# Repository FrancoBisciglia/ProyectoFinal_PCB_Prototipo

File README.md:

# ProyectoFinal_PCB_Prototipo
 PCB de la placa prototipo del Sistema de Automatización para Huertas Hidropónicas NFT

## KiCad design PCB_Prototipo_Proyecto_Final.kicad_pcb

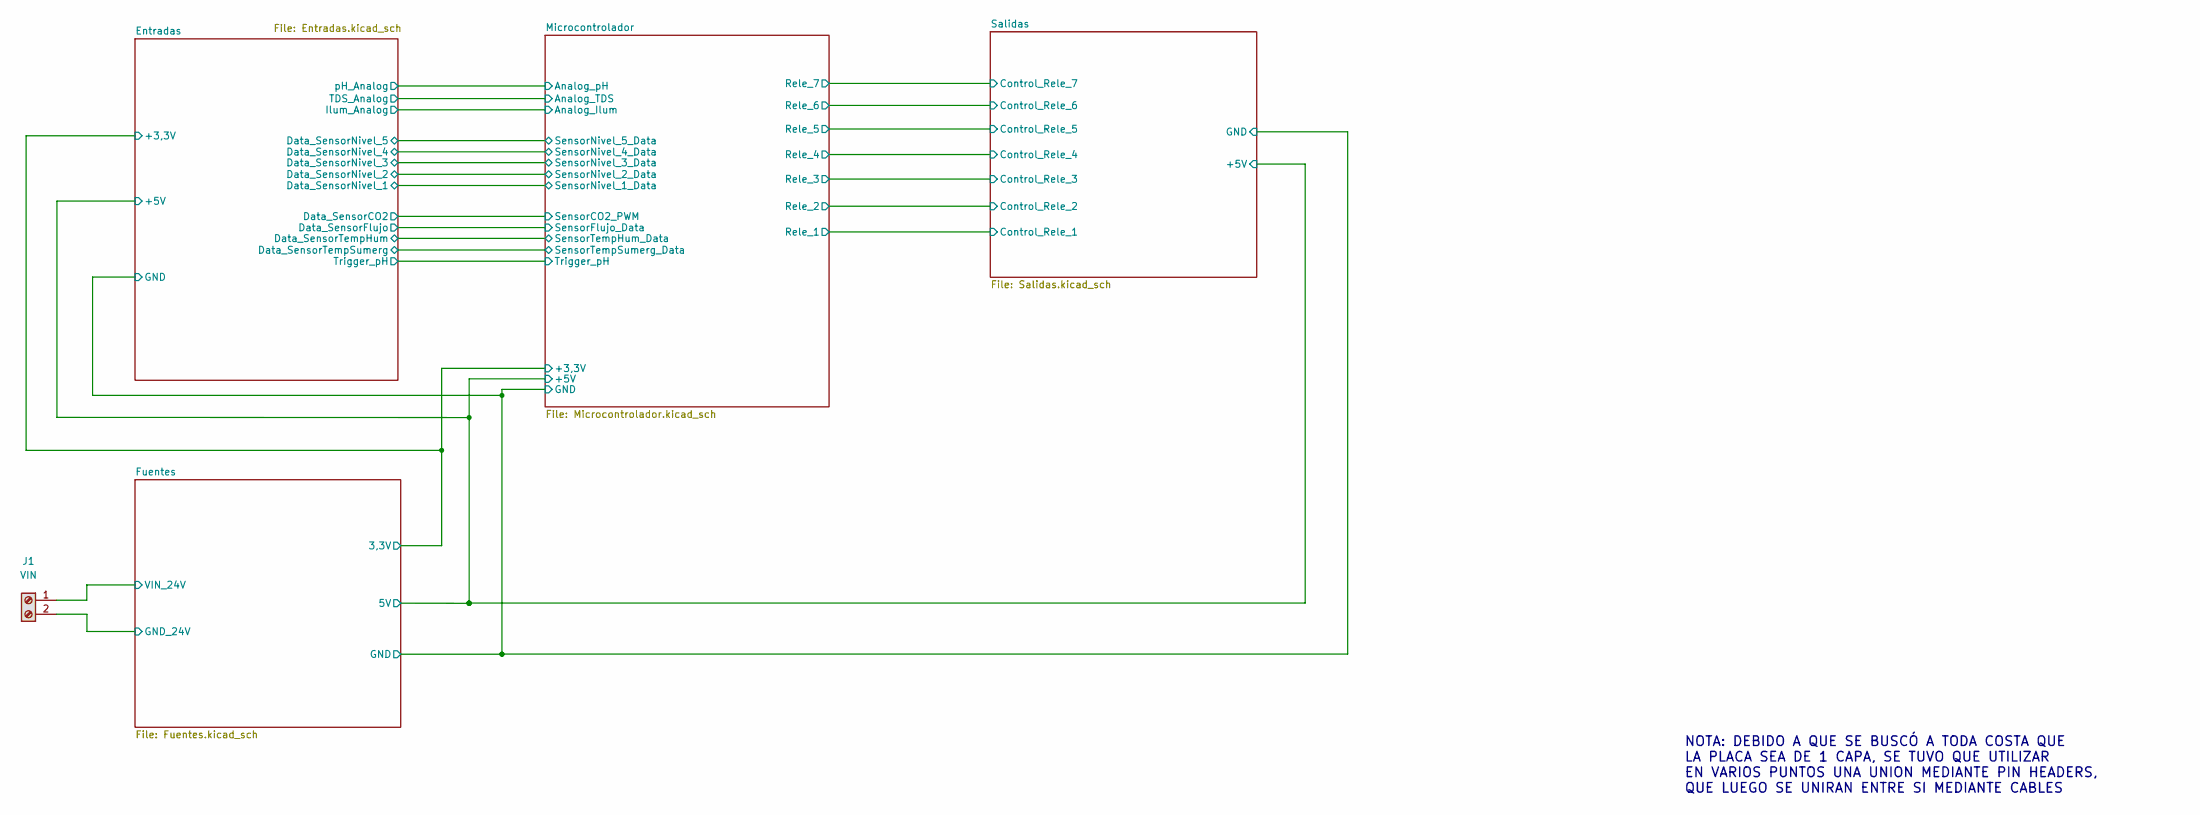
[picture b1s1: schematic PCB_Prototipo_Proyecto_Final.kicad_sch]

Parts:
J1: VIN; TB00250002BE

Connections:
/Fuentes/VIN_24V: J1.1; also elsewhere on the board
GND: J1.2; also elsewhere on the board

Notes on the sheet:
NOTA: DEBIDO A QUE SE BUSCÓ A TODA COSTA QUE LA PLACA SEA DE 1 CAPA, SE TUVO QUE UTILIZAR EN VARIOS PUNTOS UNA UNION MEDIANTE PIN HEADERS, QUE LUEGO SE UNIRAN ENTRE SI MEDIANTE CABLES

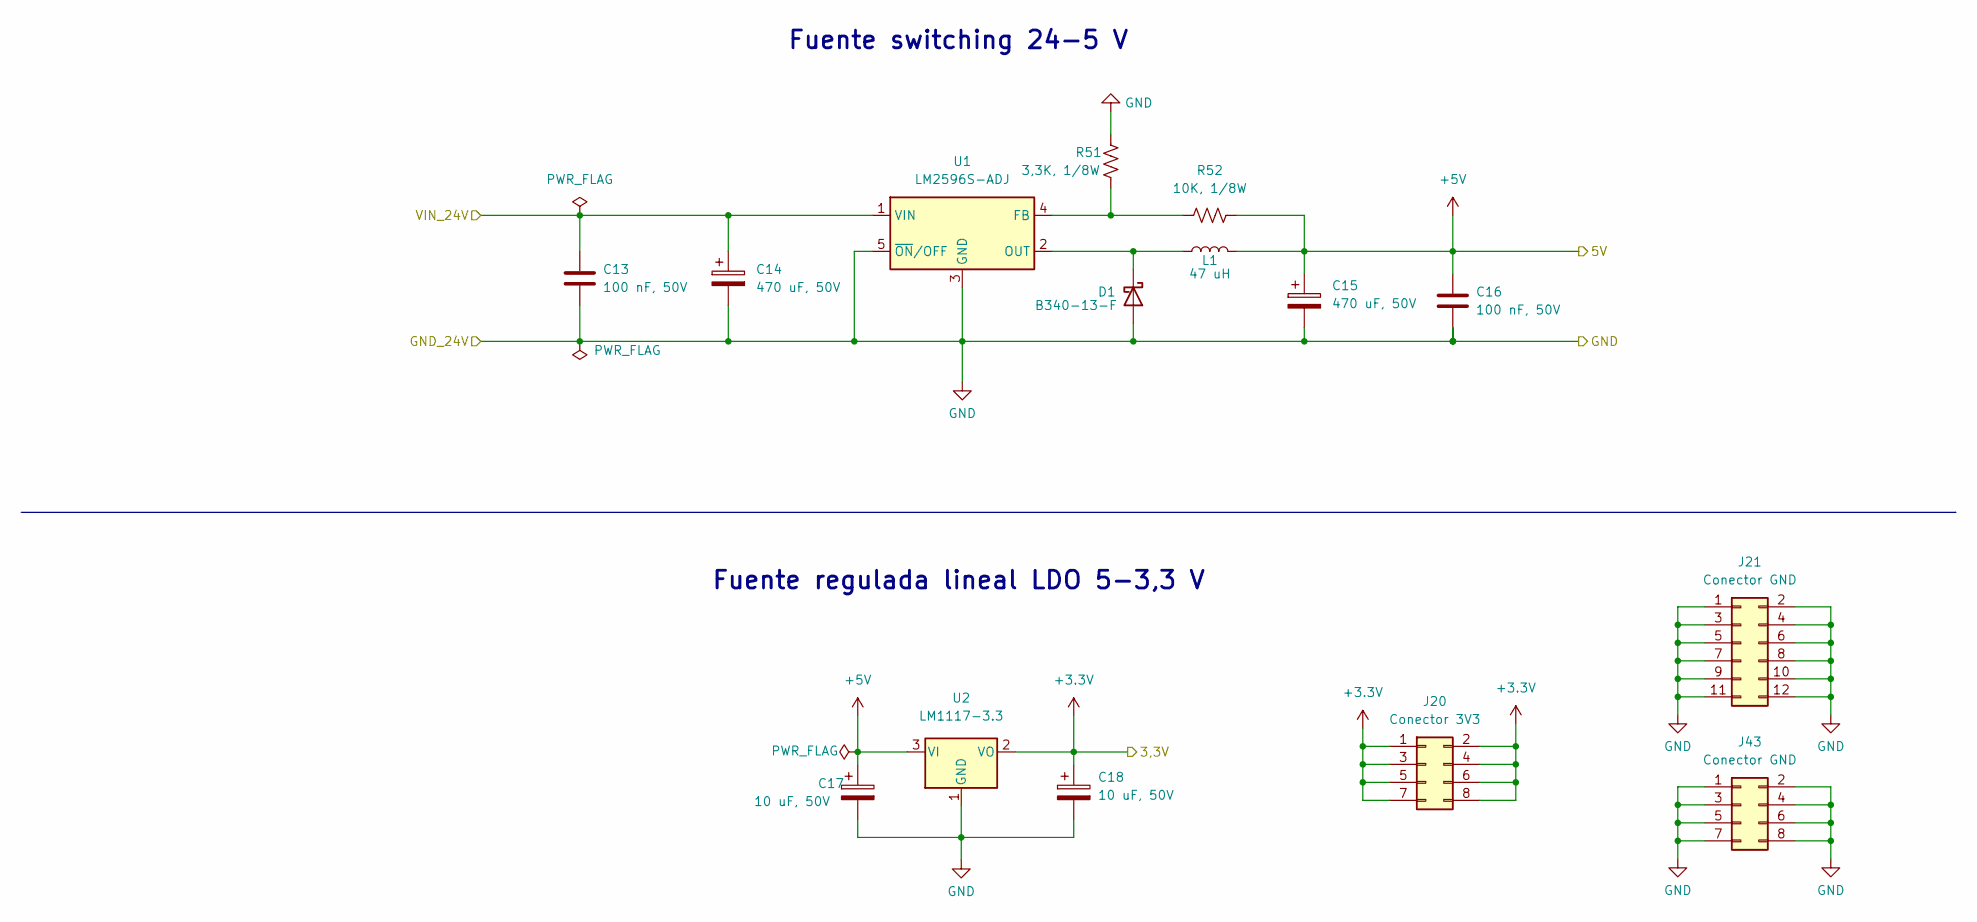
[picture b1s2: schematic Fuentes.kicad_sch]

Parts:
C13, C16: 100 nF, 50V; C_0805_2012Metric
C14, C15: 470 uF, 50V; CP_Radial_D10.0mm_P5.00mm
C17, C18: 10 uF, 50V; CP_Radial_D5.0mm_P2.00mm
D1: B340-13-F; DIOM7959X250N
J20: Conector 3V3; PinHeader_2x04_P2.54mm_Vertical
J21: Conector GND; PinHeader_2x06_P2.54mm_Vertical
J43: Conector GND; PinHeader_2x04_P2.54mm_Vertical
L1: 47 uH; L_Radial_D7.5mm_P5.00mm_Fastron_07P
R51: 3,3K, 1/8W; R_0805_2012Metric
R52: 10K, 1/8W; R_0805_2012Metric
U1: LM2596S-ADJ; LM2596SXADJNOPB
U2: LM1117-3.3; SOT230P700X180-4N

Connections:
+3.3V: C18.1, J20.1, J20.2, J20.3, J20.4, J20.5, J20.6, J20.7, J20.8, U2.2 (VO); also elsewhere on the board
+5V: C15.1, C16.1, C17.1, L1.2, R52.2, U2.3 (VI); also elsewhere on the board
/Fuentes/VIN_24V: C13.1, C14.1, U1.1 (VIN); also elsewhere on the board
GND: C13.2, C14.2, C15.2, C16.2, C17.2, C18.2, D1.2 (A), J21.1, J21.2, J21.3, J21.4, J21.5, J21.6, J21.7, J21.8, J21.9, J21.10, J21.11, J21.12, J43.1, J43.2, J43.3, J43.4, J43.5, J43.6, J43.7, J43.8, R51.1, U1.3 (GND), U1.5 (~ON/OFF), U2.1 (GND); also elsewhere on the board
unnamed: D1.1 (K), L1.1, U1.2 (OUT)
unnamed: R51.2, R52.1, U1.4 (FB)

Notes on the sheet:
Fuente switching 24-5 V
Fuente regulada lineal LDO 5-3,3 V

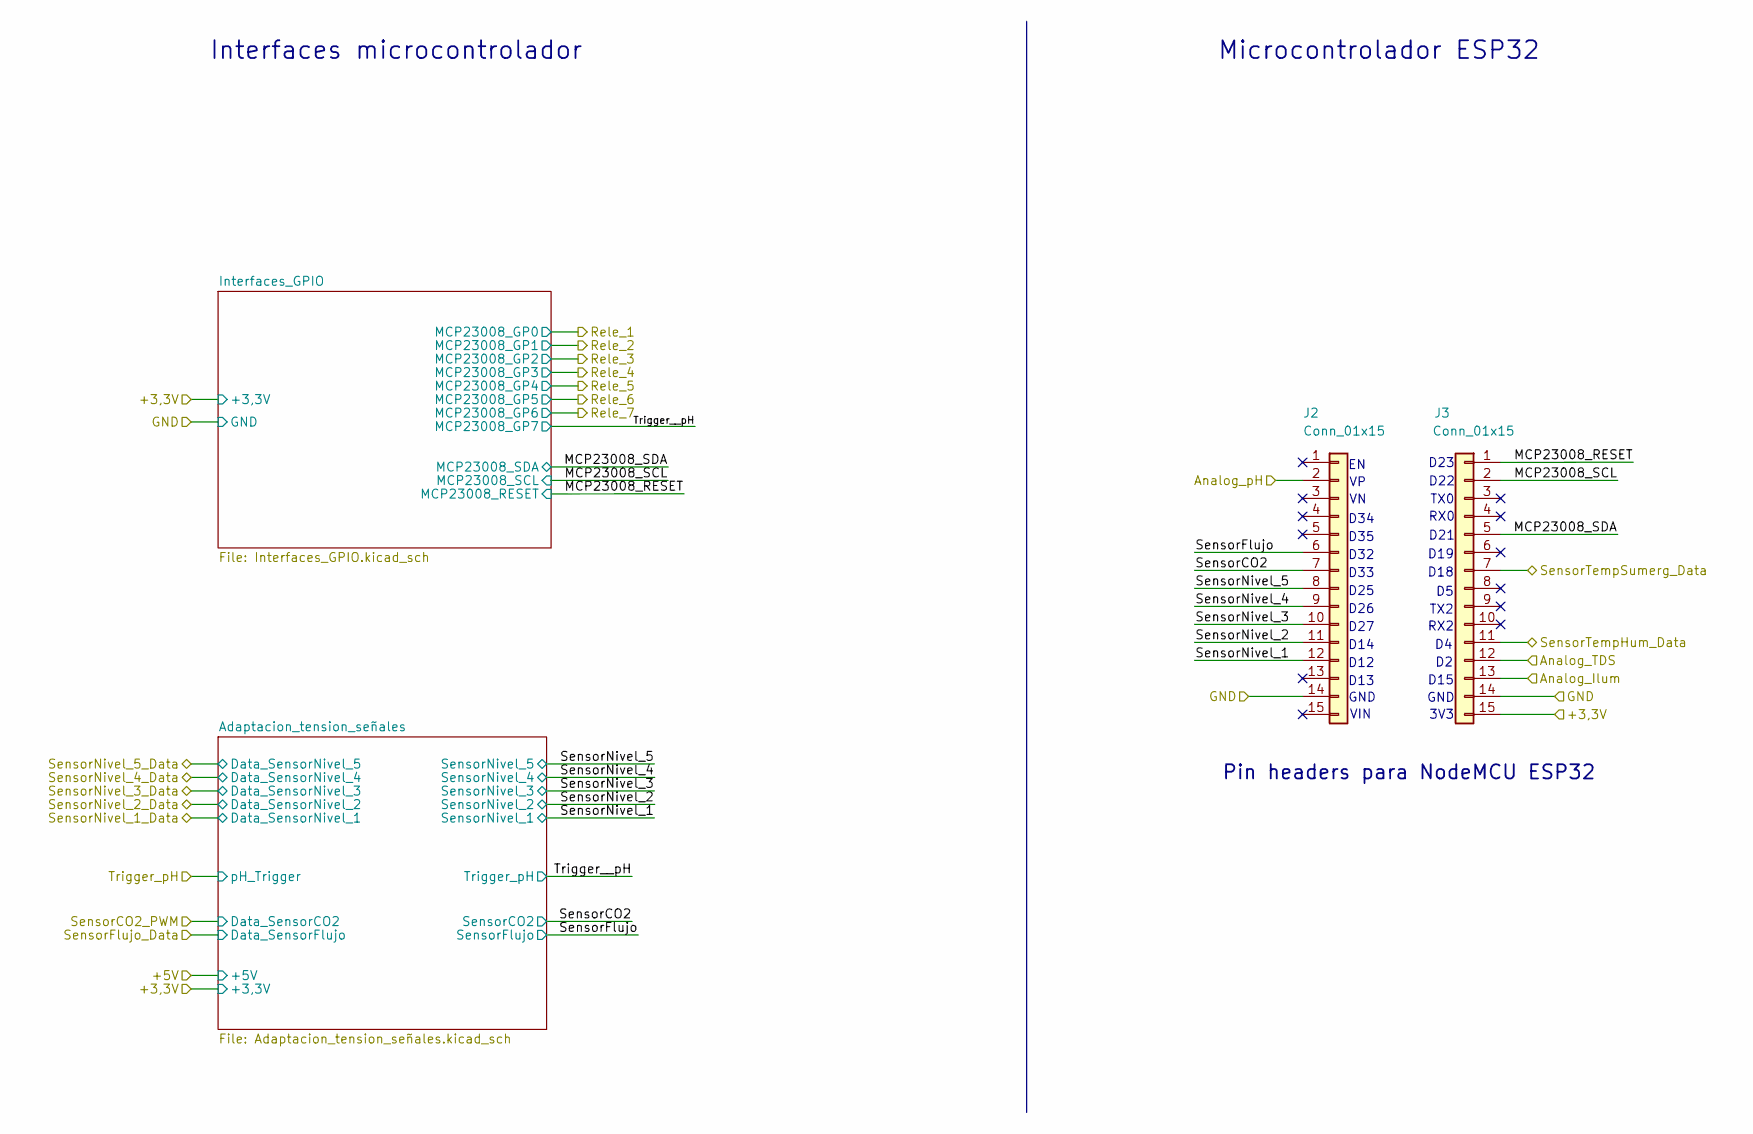
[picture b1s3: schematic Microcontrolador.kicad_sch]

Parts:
J2, J3: Conn_01x15; PinHeader_1x15_P2.54mm_Vertical

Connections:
+3.3V: J3.15; also elsewhere on the board
/Entradas/Data_SensorTempHum: J3.11; also elsewhere on the board
/Entradas/Data_SensorTempSumerg: J3.7; also elsewhere on the board
/Entradas/Ilum_Analog: J3.13; also elsewhere on the board
/Entradas/TDS_Analog: J3.12; also elsewhere on the board
/Entradas/pH_Analog: J2.2; also elsewhere on the board
/Microcontrolador/MCP23008_RESET: J3.1; also elsewhere on the board
/Microcontrolador/MCP23008_SCL: J3.2; also elsewhere on the board
/Microcontrolador/MCP23008_SDA: J3.5; also elsewhere on the board
/Microcontrolador/SensorCO2: J2.7; also elsewhere on the board
/Microcontrolador/SensorFlujo: J2.6; also elsewhere on the board
/Microcontrolador/SensorNivel_1: J2.12; also elsewhere on the board
/Microcontrolador/SensorNivel_2: J2.11; also elsewhere on the board
/Microcontrolador/SensorNivel_3: J2.10; also elsewhere on the board
/Microcontrolador/SensorNivel_4: J2.9; also elsewhere on the board
/Microcontrolador/SensorNivel_5: J2.8; also elsewhere on the board
GND: J2.14, J3.14; also elsewhere on the board

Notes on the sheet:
GND
RX2
D35
D32
D26
Microcontrolador ESP32
VIN
D18
3V3
D15
D25
D27
Interfaces microcontrolador
RX0
D34
D21
D22
D14
D13
TX0
D12
TX2
D19
D23
D33
Pin headers para NodeMCU ESP32

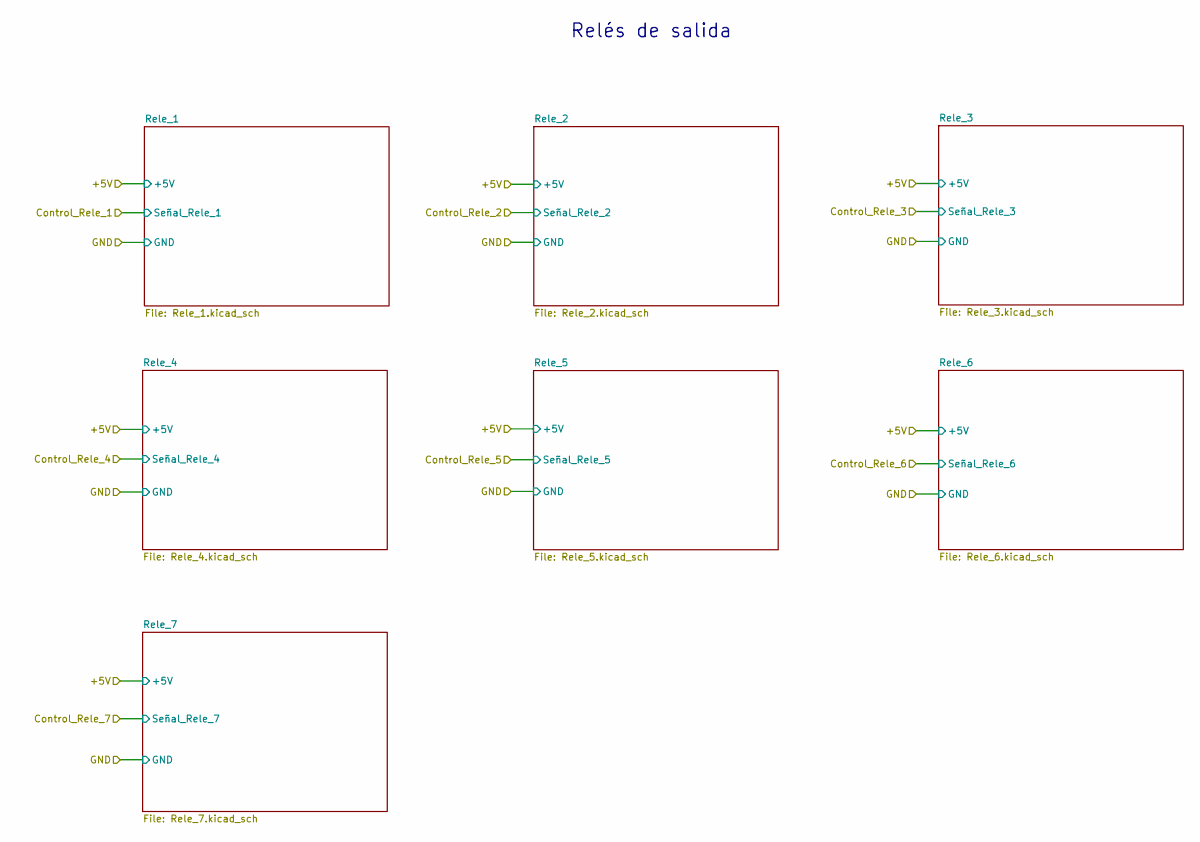
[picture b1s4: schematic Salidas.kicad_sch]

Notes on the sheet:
Relés de salida

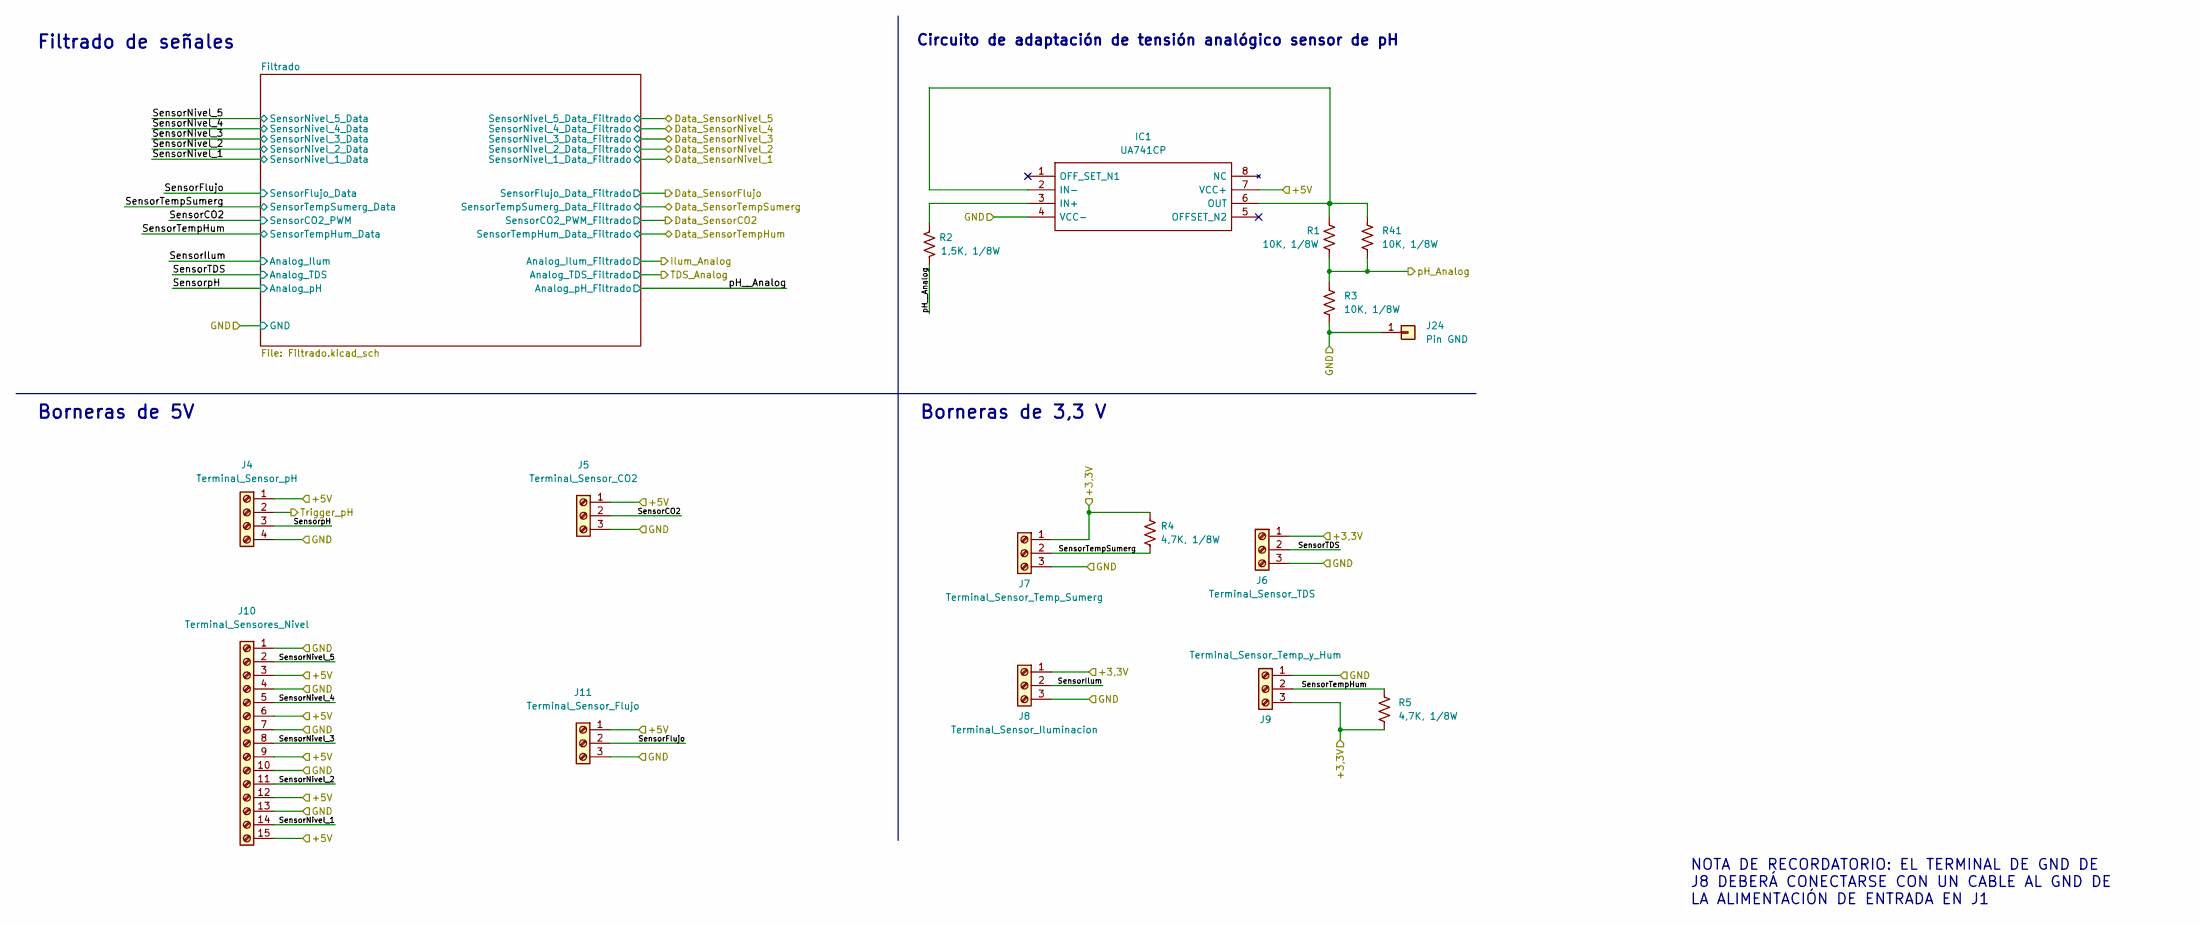
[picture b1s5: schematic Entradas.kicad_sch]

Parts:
IC1: UA741CP; DIP794W53P254L959H508Q8N; Manufacturer_Part_Number UA741CP; Mouser Part Number 595-UA741CP
J4: Terminal_Sensor_pH; TB00150004BE
J5: Terminal_Sensor_CO2; SHDR3W100P0X500_1X3_1500X760X1000P
J6: Terminal_Sensor_TDS; SHDR3W100P0X500_1X3_1500X760X1000P
J7: Terminal_Sensor_Temp_Sumerg; SHDR3W100P0X500_1X3_1500X760X1000P
J8: Terminal_Sensor_Iluminacion; SHDR3W100P0X500_1X3_1500X760X1000P
J9: Terminal_Sensor_Temp_y_Hum; SHDR3W100P0X500_1X3_1500X760X1000P
J10: Terminal_Sensores_Nivel; CUI_TB002-500-15BE
J11: Terminal_Sensor_Flujo; SHDR3W100P0X500_1X3_1500X760X1000P
J24: Pin GND; PinHeader_1x01_P2.54mm_Vertical
R1, R3, R41: 10K, 1/8W; R_0805_2012Metric
R2: 1,5K, 1/8W; R_0805_2012Metric
R4, R5: 4,7K, 1/8W; R_0805_2012Metric

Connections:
+3.3V: J6.1, J7.1, J8.1, J9.3, R4.1, R5.1; also elsewhere on the board
+5V: IC1.7 (VCC+), J4.1, J5.1, J10.3, J10.6, J10.9, J10.12, J10.15, J11.1; also elsewhere on the board
/Entradas/SensorCO2: J5.2; also elsewhere on the board
/Entradas/SensorFlujo: J11.2; also elsewhere on the board
/Entradas/SensorIlum: J8.2; also elsewhere on the board
/Entradas/SensorNivel_1: J10.14; also elsewhere on the board
/Entradas/SensorNivel_2: J10.11; also elsewhere on the board
/Entradas/SensorNivel_3: J10.8; also elsewhere on the board
/Entradas/SensorNivel_4: J10.5; also elsewhere on the board
/Entradas/SensorNivel_5: J10.2; also elsewhere on the board
/Entradas/SensorTDS: J6.2; also elsewhere on the board
/Entradas/SensorTempHum: J9.2, R5.2; also elsewhere on the board
/Entradas/SensorTempSumerg: J7.2, R4.2; also elsewhere on the board
/Entradas/SensorpH: J4.3; also elsewhere on the board
/Entradas/Trigger_pH: J4.2; also elsewhere on the board
/Entradas/pH_Analog: R1.2, R3.1, R41.2; also elsewhere on the board
/Entradas/pH__Analog: R2.2; also elsewhere on the board
GND: IC1.4 (VCC-), J4.4, J5.3, J6.3, J7.3, J8.3, J9.1, J10.1, J10.4, J10.7, J10.10, J10.13, J11.3, J24.1, R3.2; also elsewhere on the board
unnamed: IC1.2 (IN-), IC1.6 (OUT), R1.1, R41.1
unnamed: IC1.3 (IN+), R2.1

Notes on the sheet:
Filtrado de señales
NOTA DE RECORDATORIO: EL TERMINAL DE GND DE J8 DEBERÁ CONECTARSE CON UN CABLE AL GND DE LA ALIMENTACIÓN DE ENTRADA EN J1
Borneras de 5V
Borneras de 3,3 V
Circuito de adaptación de tensión analógico sensor de pH

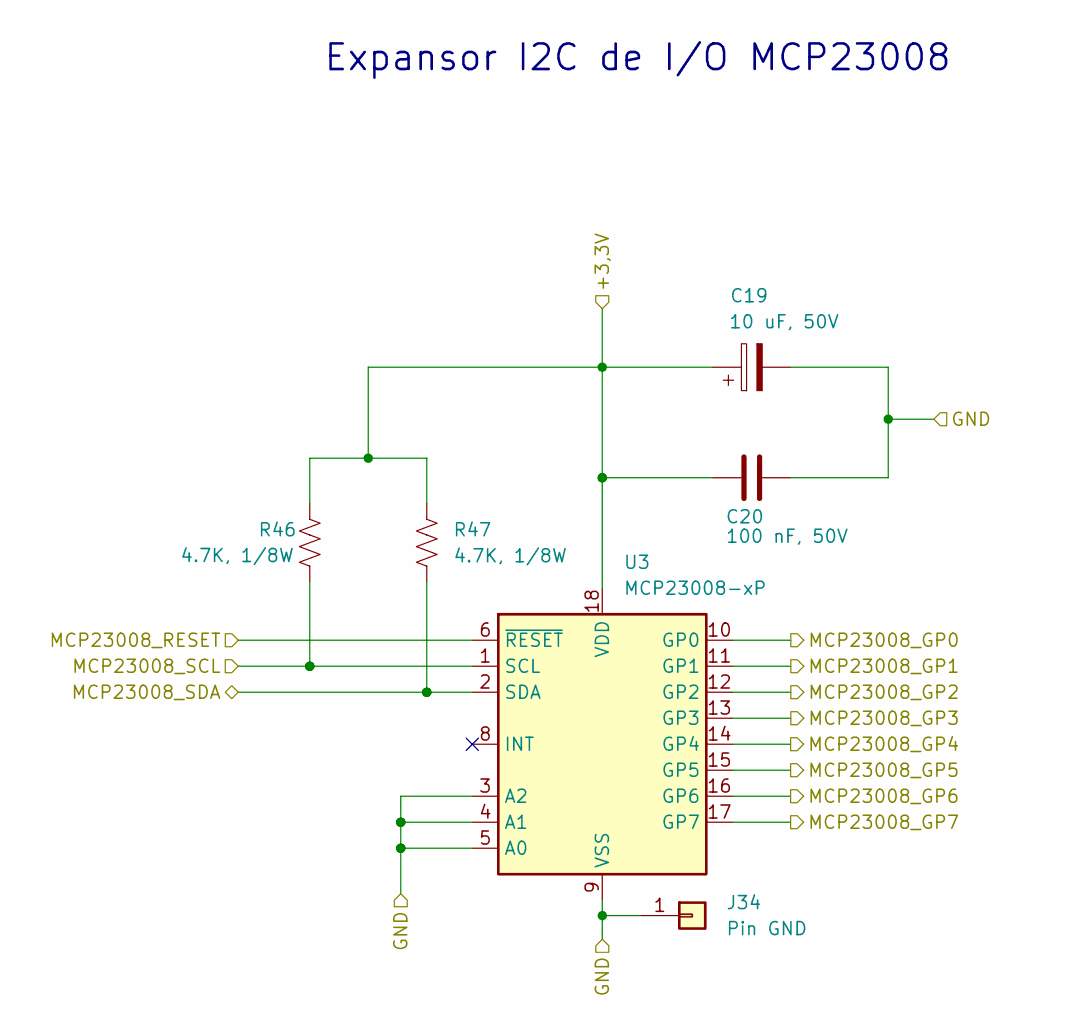
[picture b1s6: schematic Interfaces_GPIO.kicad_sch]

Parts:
C19: 10 uF, 50V; CP_Radial_D5.0mm_P2.00mm
C20: 100 nF, 50V; C_0805_2012Metric
J34: Pin GND; PinHeader_1x01_P2.54mm_Vertical
R46, R47: 4.7K, 1/8W; R_0805_2012Metric
U3: MCP23008-xP; DIP-18_W7.62mm

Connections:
+3.3V: C19.1, C20.1, R46.1, R47.1, U3.18 (VDD); also elsewhere on the board
/Microcontrolador/MCP23008_RESET: U3.6 (~RESET); also elsewhere on the board
/Microcontrolador/MCP23008_SCL: R46.2, U3.1 (SCL); also elsewhere on the board
/Microcontrolador/MCP23008_SDA: R47.2, U3.2 (SDA); also elsewhere on the board
/Microcontrolador/Rele_1: U3.10 (GP0); also elsewhere on the board
/Microcontrolador/Rele_2: U3.11 (GP1); also elsewhere on the board
/Microcontrolador/Rele_3: U3.12 (GP2); also elsewhere on the board
/Microcontrolador/Rele_4: U3.13 (GP3); also elsewhere on the board
/Microcontrolador/Rele_5: U3.14 (GP4); also elsewhere on the board
/Microcontrolador/Rele_6: U3.15 (GP5); also elsewhere on the board
/Microcontrolador/Rele_7: U3.16 (GP6); also elsewhere on the board
/Microcontrolador/Trigger__pH: U3.17 (GP7); also elsewhere on the board
GND: C19.2, C20.2, J34.1, U3.3 (A2), U3.4 (A1), U3.5 (A0), U3.9 (VSS); also elsewhere on the board

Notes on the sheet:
Expansor I2C de I/O MCP23008

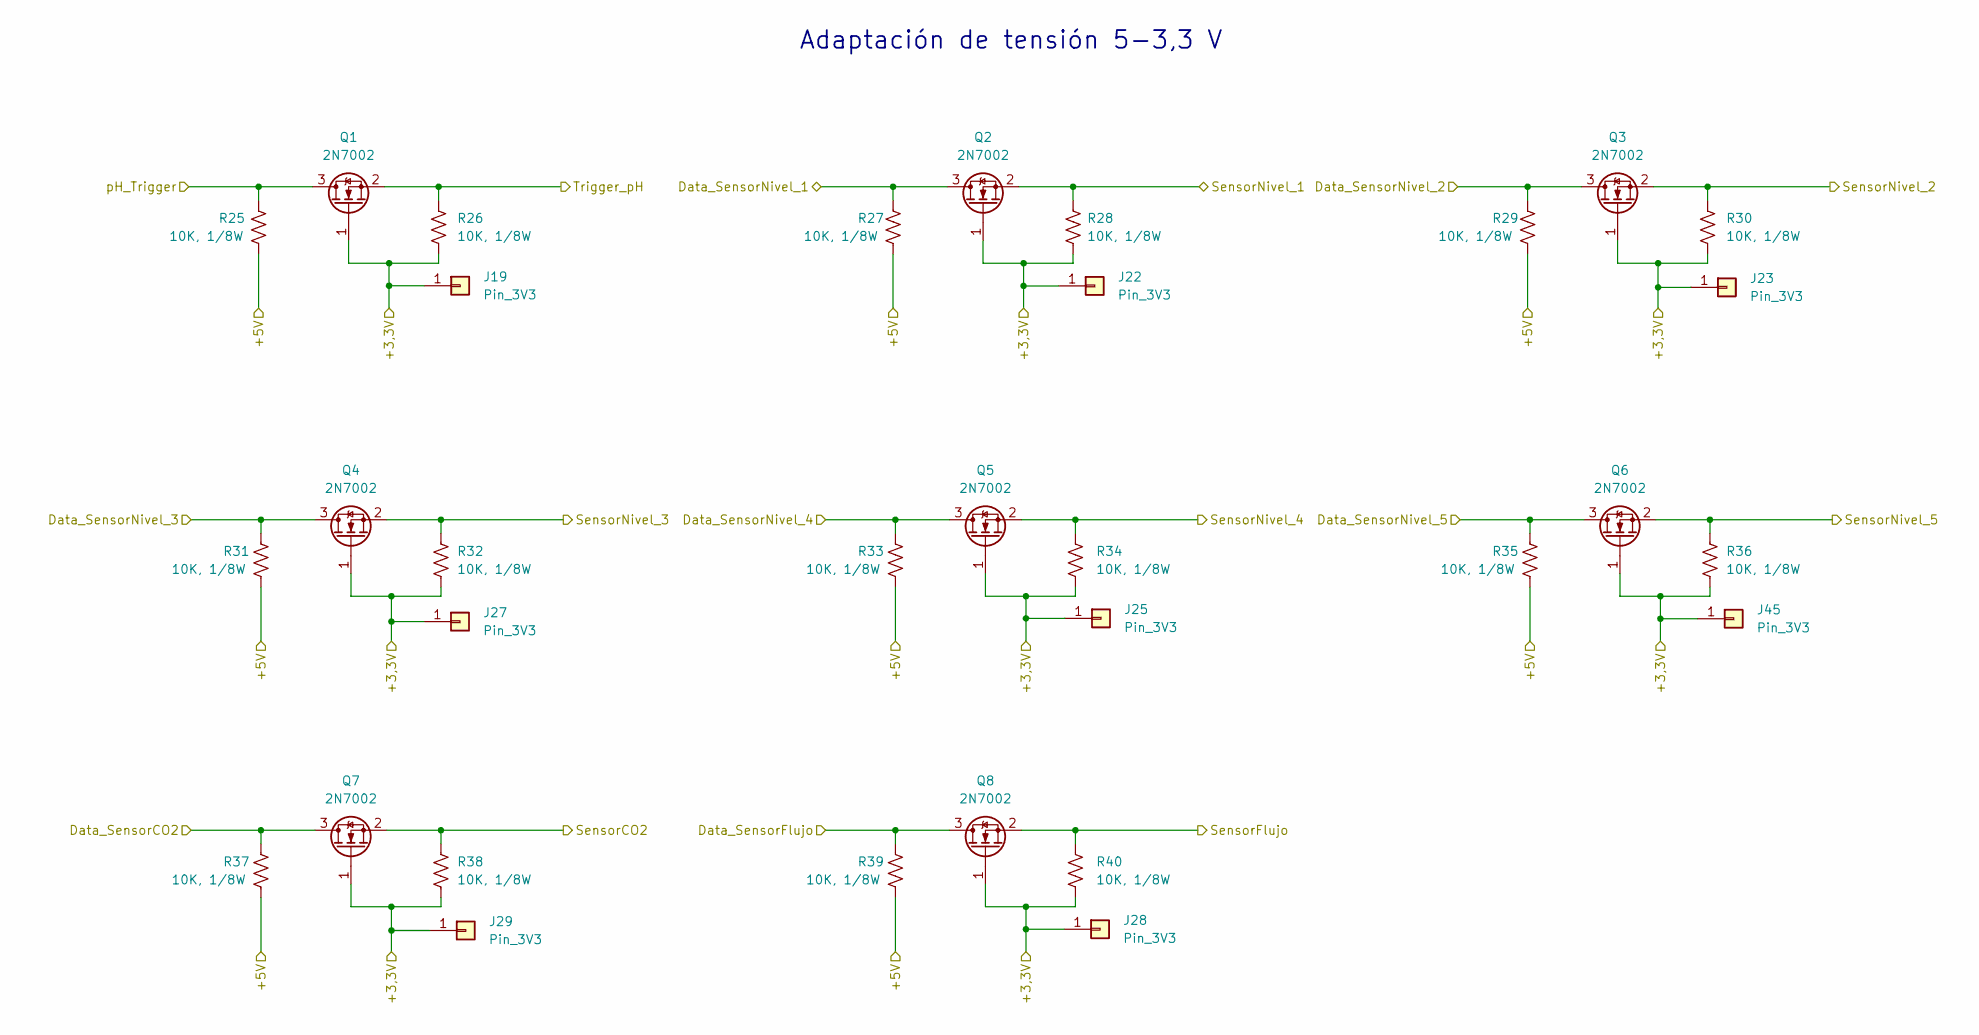
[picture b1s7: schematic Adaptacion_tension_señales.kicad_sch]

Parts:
J19, J22, J23, J25, J27, J28, J29, J45: Pin_3V3; PinHeader_1x01_P2.54mm_Vertical
Q1, Q2, Q3, Q4, Q5, Q6, Q7, Q8: 2N7002; SOT-23
R25, R26, R27, R28, R29, R30, R31, R32, R33, R34, R35, R36, R37, R38, R39, R40: 10K, 1/8W; R_0805_2012Metric

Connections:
+3.3V: J19.1, J22.1, J23.1, J25.1, J27.1, J28.1, J29.1, J45.1, Q1.1 (G), Q2.1 (G), Q3.1 (G), Q4.1 (G), Q5.1 (G), Q6.1 (G), Q7.1 (G), Q8.1 (G), R26.2, R28.2, R30.2, R32.2, R34.2, R36.2, R38.2, R40.2; also elsewhere on the board
+5V: R25.2, R27.2, R29.2, R31.2, R33.2, R35.2, R37.2, R39.2; also elsewhere on the board
/Entradas/Data_SensorCO2: Q7.3 (D), R37.1; also elsewhere on the board
/Entradas/Data_SensorFlujo: Q8.3 (D), R39.1; also elsewhere on the board
/Entradas/Data_SensorNivel_1: Q2.3 (D), R27.1; also elsewhere on the board
/Entradas/Data_SensorNivel_2: Q3.3 (D), R29.1; also elsewhere on the board
/Entradas/Data_SensorNivel_3: Q4.3 (D), R31.1; also elsewhere on the board
/Entradas/Data_SensorNivel_4: Q5.3 (D), R33.1; also elsewhere on the board
/Entradas/Data_SensorNivel_5: Q6.3 (D), R35.1; also elsewhere on the board
/Entradas/Trigger_pH: Q1.3 (D), R25.1; also elsewhere on the board
/Microcontrolador/SensorCO2: Q7.2 (S), R38.1; also elsewhere on the board
/Microcontrolador/SensorFlujo: Q8.2 (S), R40.1; also elsewhere on the board
/Microcontrolador/SensorNivel_1: Q2.2 (S), R28.1; also elsewhere on the board
/Microcontrolador/SensorNivel_2: Q3.2 (S), R30.1; also elsewhere on the board
/Microcontrolador/SensorNivel_3: Q4.2 (S), R32.1; also elsewhere on the board
/Microcontrolador/SensorNivel_4: Q5.2 (S), R34.1; also elsewhere on the board
/Microcontrolador/SensorNivel_5: Q6.2 (S), R36.1; also elsewhere on the board
/Microcontrolador/Trigger__pH: Q1.2 (S), R26.1; also elsewhere on the board

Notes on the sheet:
Adaptación de tensión 5-3,3 V

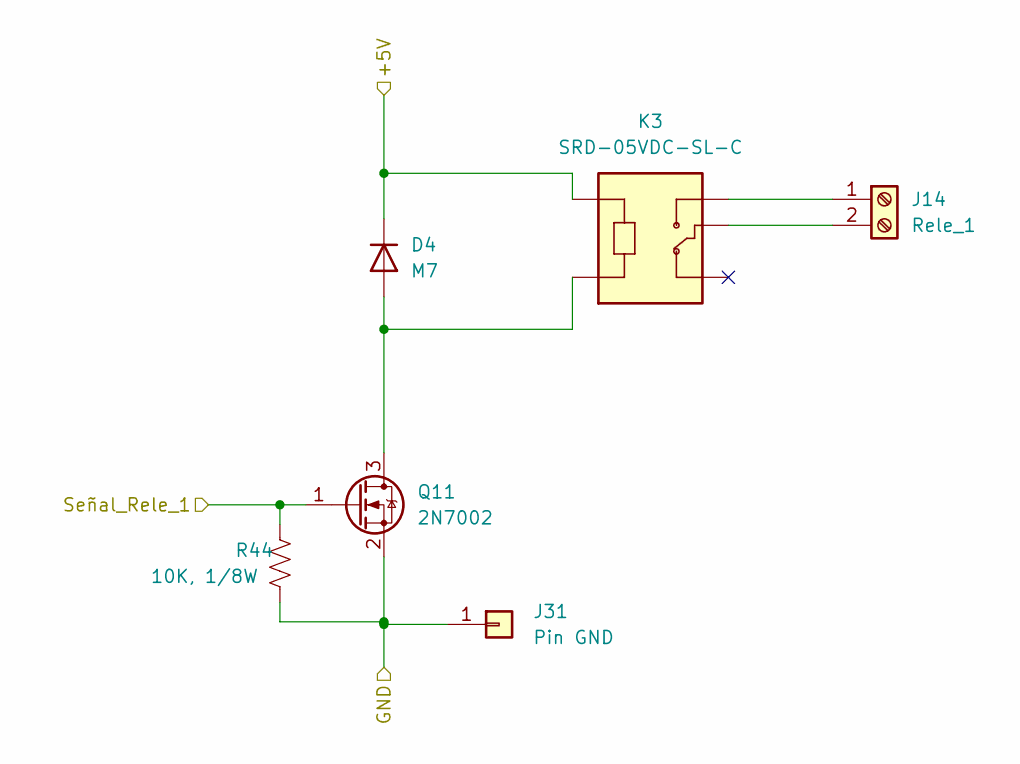
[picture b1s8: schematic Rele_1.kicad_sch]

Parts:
D4: M7; D_SMA
J14: Rele_1; TB00250002BE
J31: Pin GND; PinHeader_1x01_P2.54mm_Vertical
K3: SRD-05VDC-SL-C; RELAY_SRD-05VDC-SL-C
Q11: 2N7002; SOT-23
R44: 10K, 1/8W; R_0805_2012Metric

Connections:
+5V: D4.1 (K), K3.A1; also elsewhere on the board
/Microcontrolador/Rele_1: Q11.1 (G), R44.1; also elsewhere on the board
GND: J31.1, Q11.2 (S), R44.2; also elsewhere on the board
unnamed: D4.2 (A), K3.A2, Q11.3 (D)
unnamed: J14.1, K3.NO
unnamed: J14.2, K3.COM

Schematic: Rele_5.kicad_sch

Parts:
D5: M7; D_SMA
J15: Rele_5; TB00250002BE
J32: Pin GND; PinHeader_1x01_P2.54mm_Vertical
K4: SRD-05VDC-SL-C; RELAY_SRD-05VDC-SL-C
Q12: 2N7002; SOT-23
R45: 10K, 1/8W; R_0805_2012Metric

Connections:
+5V: D5.1 (K), K4.A1; also elsewhere on the board
/Microcontrolador/Rele_5: Q12.1 (G), R45.1; also elsewhere on the board
GND: J32.1, Q12.2 (S), R45.2; also elsewhere on the board
unnamed: D5.2 (A), K4.A2, Q12.3 (D)
unnamed: J15.1, K4.NO
unnamed: J15.2, K4.COM

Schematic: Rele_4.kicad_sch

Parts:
D2: M7; D_SMA
J12: Rele_4; TB00250002BE
J30: Pin GND; PinHeader_1x01_P2.54mm_Vertical
K1: SRD-05VDC-SL-C; RELAY_SRD-05VDC-SL-C
Q9: 2N7002; SOT-23
R42: 10K, 1/8W; R_0805_2012Metric

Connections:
+5V: D2.1 (K), K1.A1; also elsewhere on the board
/Microcontrolador/Rele_4: Q9.1 (G), R42.1; also elsewhere on the board
GND: J30.1, Q9.2 (S), R42.2; also elsewhere on the board
unnamed: D2.2 (A), K1.A2, Q9.3 (D)
unnamed: J12.1, K1.NO
unnamed: J12.2, K1.COM

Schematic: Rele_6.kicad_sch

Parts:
D8: M7; D_SMA
J18: Rele_6; TB00250002BE
J36: Pin GND; PinHeader_1x01_P2.54mm_Vertical
K7: SRD-05VDC-SL-C; RELAY_SRD-05VDC-SL-C
Q15: 2N7002; SOT-23
R50: 10K, 1/8W; R_0805_2012Metric

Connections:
+5V: D8.1 (K), K7.A1; also elsewhere on the board
/Microcontrolador/Rele_6: Q15.1 (G), R50.1; also elsewhere on the board
GND: J36.1, Q15.2 (S), R50.2; also elsewhere on the board
unnamed: D8.2 (A), K7.A2, Q15.3 (D)
unnamed: J18.1, K7.NO
unnamed: J18.2, K7.COM

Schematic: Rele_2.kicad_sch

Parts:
D6: M7; D_SMA
J16: Rele_2; TB00250002BE
J33: Pin GND; PinHeader_1x01_P2.54mm_Vertical
K5: SRD-05VDC-SL-C; RELAY_SRD-05VDC-SL-C
Q13: 2N7002; SOT-23
R48: 10K, 1/8W; R_0805_2012Metric

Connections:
+5V: D6.1 (K), K5.A1; also elsewhere on the board
/Microcontrolador/Rele_2: Q13.1 (G), R48.1; also elsewhere on the board
GND: J33.1, Q13.2 (S), R48.2; also elsewhere on the board
unnamed: D6.2 (A), K5.A2, Q13.3 (D)
unnamed: J16.1, K5.NO
unnamed: J16.2, K5.COM

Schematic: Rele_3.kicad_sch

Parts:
D7: M7; D_SMA
J17: Rele_3; TB00250002BE
J35: Pin GND; PinHeader_1x01_P2.54mm_Vertical
K6: SRD-05VDC-SL-C; RELAY_SRD-05VDC-SL-C
Q14: 2N7002; SOT-23
R49: 10K, 1/8W; R_0805_2012Metric

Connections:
+5V: D7.1 (K), K6.A1; also elsewhere on the board
/Microcontrolador/Rele_3: Q14.1 (G), R49.1; also elsewhere on the board
GND: J35.1, Q14.2 (S), R49.2; also elsewhere on the board
unnamed: D7.2 (A), K6.A2, Q14.3 (D)
unnamed: J17.1, K6.NO
unnamed: J17.2, K6.COM

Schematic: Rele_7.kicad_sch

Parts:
D3: M7; D_SMA
J13: Rele_7; TB00250002BE
J44: Pin GND; PinHeader_1x01_P2.54mm_Vertical
K2: SRD-05VDC-SL-C; RELAY_SRD-05VDC-SL-C
Q10: 2N7002; SOT-23
R43: 10K, 1/8W; R_0805_2012Metric

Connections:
+5V: D3.1 (K), K2.A1; also elsewhere on the board
/Microcontrolador/Rele_7: Q10.1 (G), R43.1; also elsewhere on the board
GND: J44.1, Q10.2 (S), R43.2; also elsewhere on the board
unnamed: D3.2 (A), K2.A2, Q10.3 (D)
unnamed: J13.1, K2.NO
unnamed: J13.2, K2.COM

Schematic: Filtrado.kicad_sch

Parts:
C1, C2, C3, C4, C5, C6, C7, C8, C9, C10, C11, C12: 1 nF; C_0805_2012Metric
J26, J37, J38, J39, J40, J41, J42, J46, J47: Pin GND; PinHeader_1x01_P2.54mm_Vertical
R6, R7, R8, R9, R10, R11, R12, R13, R14, R15, R16, R17, R18, R19, R20, R21, R22, R23, R24: 50, 1/8W; R_0805_2012Metric

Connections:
/Entradas/Data_SensorCO2: C6.1, R16.2; also elsewhere on the board
/Entradas/Data_SensorFlujo: C11.1, R23.2; also elsewhere on the board
/Entradas/Data_SensorNivel_1: R7.2; also elsewhere on the board
/Entradas/Data_SensorNivel_2: R9.2; also elsewhere on the board
/Entradas/Data_SensorNivel_3: R11.2; also elsewhere on the board
/Entradas/Data_SensorNivel_4: R13.2; also elsewhere on the board
/Entradas/Data_SensorNivel_5: R15.2; also elsewhere on the board
/Entradas/Data_SensorTempHum: R22.2; also elsewhere on the board
/Entradas/Data_SensorTempSumerg: R18.2; also elsewhere on the board
/Entradas/Ilum_Analog: C9.1, R20.2; also elsewhere on the board
/Entradas/SensorCO2: R16.1; also elsewhere on the board
/Entradas/SensorFlujo: R23.1; also elsewhere on the board
/Entradas/SensorIlum: R20.1; also elsewhere on the board
/Entradas/SensorNivel_1: R6.1; also elsewhere on the board
/Entradas/SensorNivel_2: R8.1; also elsewhere on the board
/Entradas/SensorNivel_3: R10.1; also elsewhere on the board
/Entradas/SensorNivel_4: R12.1; also elsewhere on the board
/Entradas/SensorNivel_5: R14.1; also elsewhere on the board
/Entradas/SensorTDS: R19.1; also elsewhere on the board
/Entradas/SensorTempHum: R21.1; also elsewhere on the board
/Entradas/SensorTempSumerg: R17.1; also elsewhere on the board
/Entradas/SensorpH: R24.1; also elsewhere on the board
/Entradas/TDS_Analog: C8.1, R19.2; also elsewhere on the board
/Entradas/pH__Analog: C12.1, R24.2; also elsewhere on the board
GND: C1.2, C2.2, C3.2, C4.2, C5.2, C6.2, C7.2, C8.2, C9.2, C10.2, C11.2, C12.2, J26.1, J37.1, J38.1, J39.1, J40.1, J41.1, J42.1, J46.1, J47.1; also elsewhere on the board
unnamed: C1.1, R6.2, R7.1
unnamed: C2.1, R8.2, R9.1
unnamed: C3.1, R10.2, R11.1
unnamed: C4.1, R12.2, R13.1
unnamed: C5.1, R14.2, R15.1
unnamed: C7.1, R17.2, R18.1
unnamed: C10.1, R21.2, R22.1

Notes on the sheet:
Filtrado de señales analógicas y digitales de sensores
